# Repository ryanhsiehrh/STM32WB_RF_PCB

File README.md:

# STM32WB_RF_PCB
Custom 4-layer developement board centered around the STM32WB55CEU6 MCU. The board includes 2.4GHz BLE RF cicuitry, ESD protected USB, SWD, and communication interfaces: UART, I2C, SPI, GPIO.

---

# Components

* **Microcontroller**: STM32WB55CEU6 
* **Power Supply**: USB Type-C stepped down through a 3.3V LDO regulator.
* **Clock:** Dual high-speed external (32 MHz) and low-speed external (32.768 kHz) crystal oscillators.
* **Wireless & RF:** 2.4 GHz RF featuring an impedance-matched filter network and $50\Omega$ trace feeding a U.FL antenna connector.
* **USB & Protection:** USB Type-C interface with a USBLC6-2SC6 ESD protection IC on $90\Omega$ differential data pairs.
* **Peripherals & Interfaces:** General-Purpose I/O (I/O and Analog), I2C, SPI, and UART headers
* **Debug & User Controls:** Tag-Connect SWD programming header, BOOT0 switch, and user status LED.
* **PCB Stackup:** GND planes on layers 1-3, 3V3 plane on layer 4, and contains via stiching to limit interference between planes.

---

**Schematic:**

**PCB:**

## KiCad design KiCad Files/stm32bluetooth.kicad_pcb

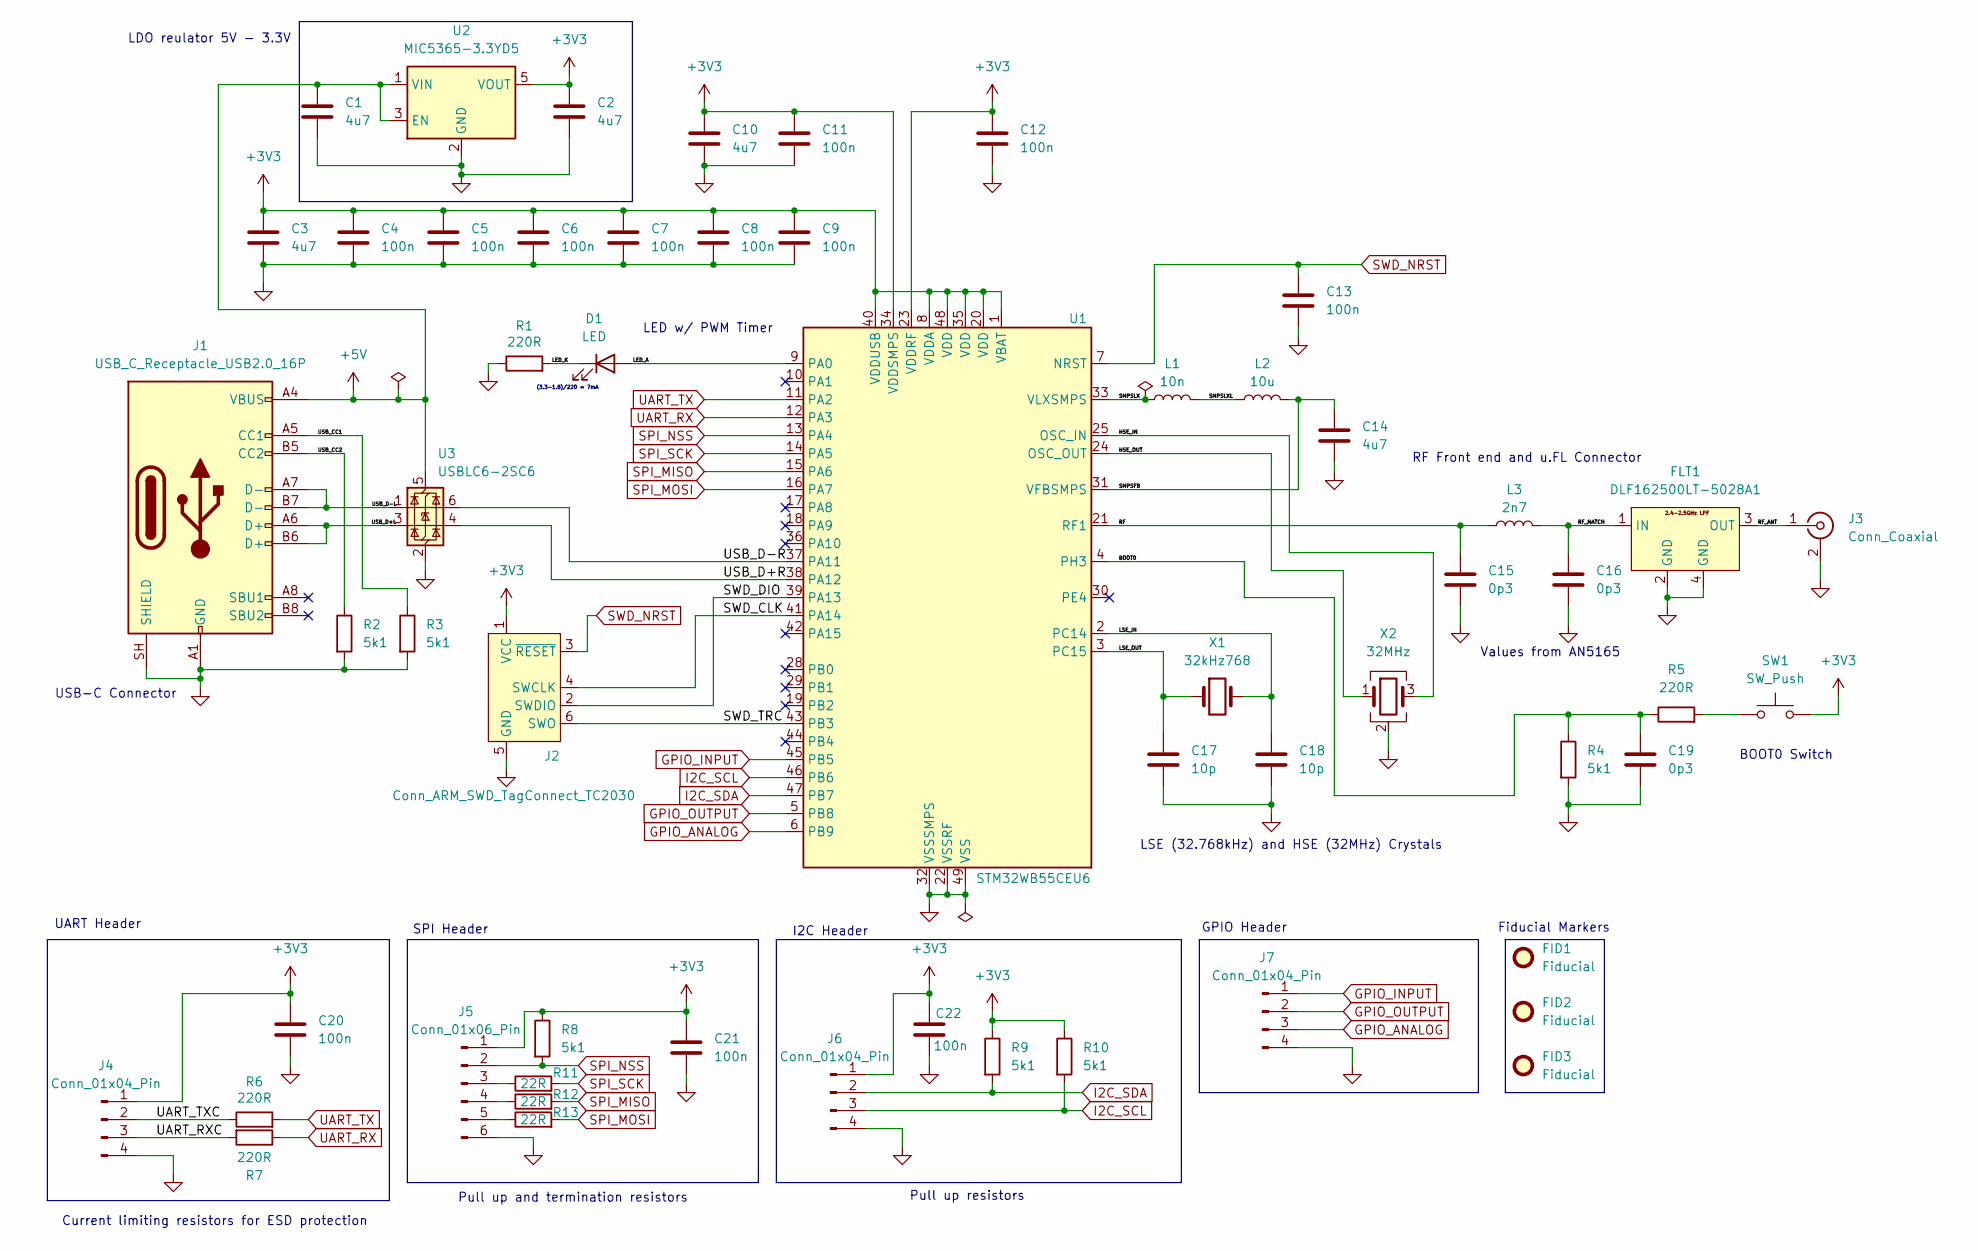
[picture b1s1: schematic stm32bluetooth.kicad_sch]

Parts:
C1, C2, C3, C10, C14: 4u7; C_0603_1608Metric
C4, C5, C6, C7, C8, C9, C11, C12, C13, C20, C21, C22: 100n; C_0402_1005Metric
C15, C16, C19: 0p3; C_0402_1005Metric
C17, C18: 10p; C_0603_1608Metric
D1: LED; LED_0402_1005Metric
FID1, FID2, FID3: Fiducial; Fiducial_1mm_Mask2mm
FLT1: DLF162500LT-5028A1
J1: USB_C_Receptacle_USB2.0_16P; USB_C_Receptacle_GCT_USB4105-xx-A_16P_TopMnt_Horizontal
J2: Conn_ARM_SWD_TagConnect_TC2030; Tag-Connect_TC2030-IDC-FP_2x03_P1.27mm_Vertical
J3: Conn_Coaxial; U.FL_Hirose_U.FL-R-SMT-1_Vertical
J4, J6, J7: Conn_01x04_Pin; PinHeader_1x04_P2.54mm_Vertical
J5: Conn_01x06_Pin; PinHeader_1x06_P2.54mm_Vertical
L1: 10n; L_0402_1005Metric
L2: 10u; L_0805_2012Metric
L3: 2n7; L_0402_1005Metric
R1, R5, R6, R7: 220R; R_0402_1005Metric
R2, R3, R4, R8, R9, R10: 5k1; R_0402_1005Metric
R11, R12, R13: 22R; R_0402_1005Metric
SW1: SW_Push; SW_SPST_B3U-1000P-B
U1: STM32WB55CEU6; QFN-48-1EP_7x7mm_P0.5mm_EP5.6x5.6mm
U2: MIC5365-3.3YD5; TSOT-23-5
U3: USBLC6-2SC6; SOT-23-6
X1: 32kHz768; Crystal_SMD_2012-2Pin_2.0x1.2mm
X2: 32MHz; Crystal_SMD_2016-4Pin_2.0x1.6mm

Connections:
+3V3: C2.1, C3.1, C4.2, C5.1, C6.1, C7.1, C8.1, C9.1, C10.1, C11.2, C12.1, C20.1, C21.1, C22.1, J2.1 (VCC), J4.1, J5.1, J6.1, R8.1, R9.1, R10.1, SW1.2, U1.1 (VBAT), U1.8 (VDDA), U1.20 (VDD), U1.23 (VDDRF), U1.34 (VDDSMPS), U1.35 (VDD), U1.40 (VDDUSB), U1.48 (VDD), U2.5 (VOUT)
+5V: C1.1, J1.A4 (VBUS), J1.A9 (VBUS), J1.B4 (VBUS), J1.B9 (VBUS), U2.1 (VIN), U2.3 (EN), U3.5 (VBUS)
/BOOT0: C19.1, R4.1, R5.1, U1.4 (PH3)
/HSE_IN: U1.25 (OSC_IN), X2.3
/HSE_OUT: U1.24 (OSC_OUT), X2.1
/LED_A: D1.2 (A), U1.9 (PA0)
/LED_K: D1.1 (K), R1.2
/LSE_IN: C18.1, U1.2 (PC14), X1.2
/LSE_OUT: C17.1, U1.3 (PC15), X1.1
/RF: C15.1, L3.1, U1.21 (RF1)
/RF_ANT: FLT1.3 (OUT), J3.1 (In)
/RF_MATCH: C16.1, FLT1.1 (IN), L3.2
/SMPSFB: C14.1, L2.2, U1.31 (VFBSMPS)
/SMPSLX: L1.1, U1.33 (VLXSMPS)
/SMPSLXL: L1.2, L2.1
/SWD_CLK: J2.4 (SWCLK), U1.41 (PA14)
/SWD_DIO: J2.2 (SWDIO), U1.39 (PA13)
/SWD_TRC: J2.6 (SWO), U1.43 (PB3)
/UART_RXC: J4.3, R7.2
/UART_TXC: J4.2, R6.1
/USB_CC1: J1.A5 (CC1), R3.1
/USB_CC2: J1.B5 (CC2), R2.1
/USB_D+L: J1.A6 (D+), J1.B6 (D+), U3.3 (I/O2)
/USB_D+R: U1.38 (PA12), U3.4 (I/O2)
/USB_D-L: J1.A7 (D-), J1.B7 (D-), U3.1 (I/O1)
/USB_D-R: U1.37 (PA11), U3.6 (I/O1)
GND: C1.2, C2.2, C3.2, C4.1, C5.2, C6.2, C7.2, C8.2, C9.2, C10.2, C11.1, C12.2, C13.2, C14.2, C15.2, C16.2, C17.2, C18.2, C19.2, C20.2, C21.2, C22.2, FLT1.2 (GND), FLT1.4 (GND), J1.A1 (GND), J1.A12 (GND), J1.B1 (GND), J1.B12 (GND), J1.SH (SHIELD), J2.5 (GND), J3.2 (Ext), J4.4, J5.6, J6.4, J7.4, R1.1, R2.2, R3.2, R4.2, U1.22 (VSSRF), U1.32 (VSSSMPS), U1.49 (VSS), U2.2 (GND), U3.2 (GND), X2.2 (G), X2.4 (G)
GPIO_ANALOG: J7.3, U1.6 (PB9)
GPIO_INPUT: J7.1, U1.45 (PB5)
GPIO_OUTPUT: J7.2, U1.5 (PB8)
I2C_SCL: J6.3, R10.2, U1.46 (PB6)
I2C_SDA: J6.2, R9.2, U1.47 (PB7)
unnamed: J5.3, R11.1
unnamed: J5.4, R12.1
unnamed: J5.5, R13.1
unnamed: R5.2, SW1.1
SPI_MISO: R12.2, U1.15 (PA6)
SPI_MOSI: R13.2, U1.16 (PA7)
SPI_NSS: J5.2, R8.2, U1.13 (PA4)
SPI_SCK: R11.2, U1.14 (PA5)
SWD_NRST: C13.1, J2.3 (~RESET), U1.7 (NRST)
UART_RX: R7.1, U1.12 (PA3)
UART_TX: R6.2, U1.11 (PA2)

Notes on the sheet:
RF Front end and u.FL Connector
Current limiting resistors for ESD protection
Pull up resistors
LDO reulator 5V - 3.3V
USB-C Connector
GPIO Header
(3.3-1.8)/220 = 7mA
Fiducial Markers
Values from AN5165
SPI Header
LSE (32.768kHz) and HSE (32MHz) Crystals
UART Header
Pull up and termination resistors
I2C Header
LED w/ PWM Timer
BOOT0 Switch

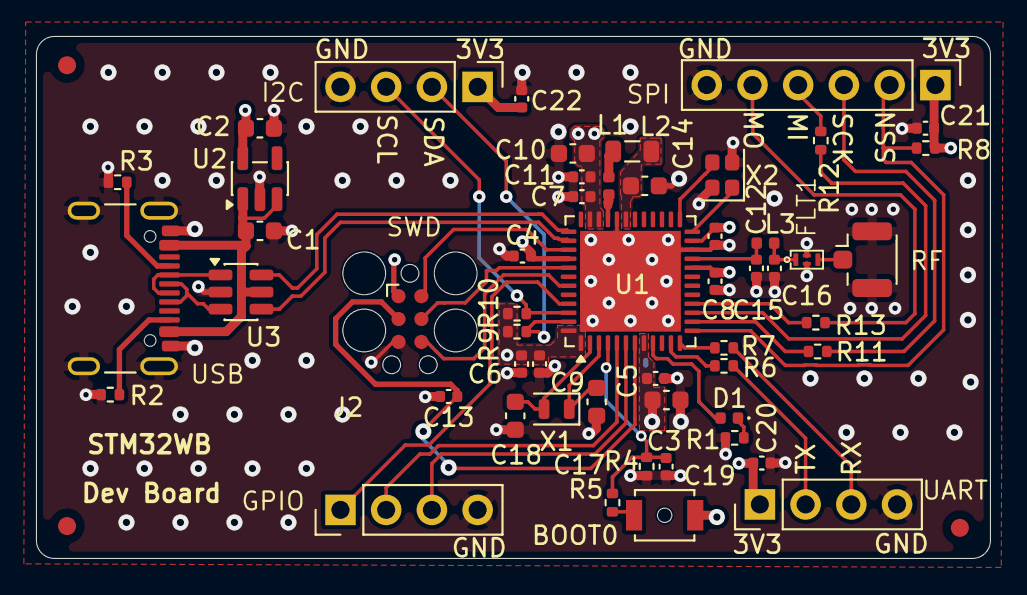
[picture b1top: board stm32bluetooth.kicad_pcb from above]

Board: 4 copper layers, 53.0 x 29.0 mm, 56 parts (0 on the bottom side), 43 nets.
